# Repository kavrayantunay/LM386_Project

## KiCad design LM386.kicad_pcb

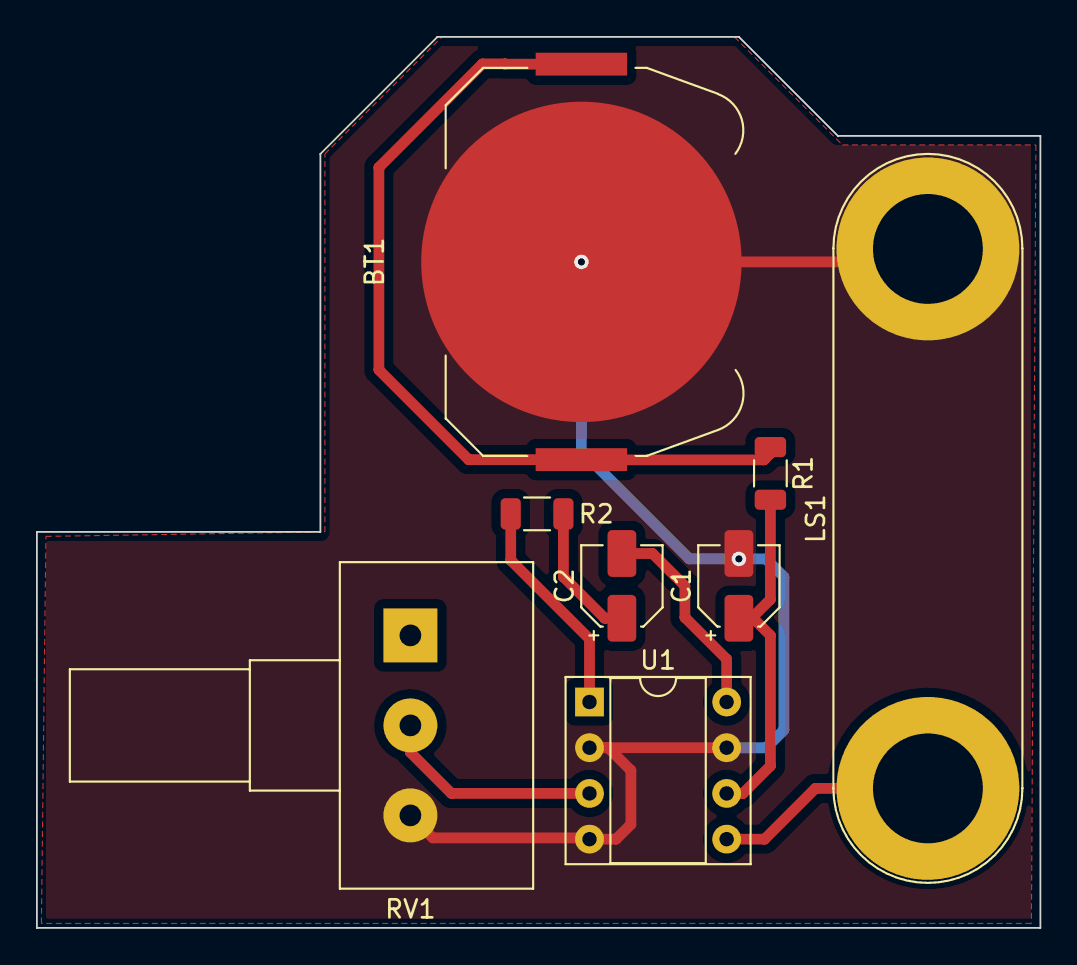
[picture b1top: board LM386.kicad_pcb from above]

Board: 2 copper layers, 55.8 x 49.5 mm, 8 parts (0 on the bottom side), 8 nets.

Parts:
BT1: Battery; BatteryHolder_Keystone_3034_1x20mm
C1: 220uF; CP_Elec_4x5.4
C2: 10uF; CP_Elec_4x5.4
LS1: Speaker; Banana_Jack_2Pin
R1: 10; R_1206_3216Metric
R2: 1k; R_1206_3216Metric
RV1: 10k; Potentiometer_Alps_RK163_Single_Horizontal
U1: LM386; DIP-8_W7.62mm_Socket

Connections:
GND: BT1.2 (-), C1.2, LS1.2, RV1.3, U1.2 (-), U1.4 (GND), U1.7 (BYPASS)
unnamed: BT1.1 (+), R1.1
unnamed: C1.1, R1.2, U1.6 (V+)
unnamed: C2.1, R2.1
unnamed: C2.2, U1.8 (GAIN)
unnamed: LS1.1, U1.5
unnamed: R2.2, U1.1 (GAIN)
unnamed: RV1.2, U1.3 (+)
